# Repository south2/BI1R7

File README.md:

# body interaction vibrator development board

body interaction 1 board, revision 7

The *body interaction 1* is a tiny microcontroller board for building vibrating devices like (sex) toys. 
The vibration strength is controlled by motion. It is equipped with a radio module for wireless data transmission. 
The *body interaction 1* includes a LiPo battery and a capsuled vibration motor. 
Supports the Arduino IDE and Codebender.

*body interaction 1* is small, cheap and you can start at once. You can program the board with the Arduino software (IDE) or in a web browser (eg. codebender). A demo sketch is already uploaded to the board. Download 3D cases from [Thingiverse](http://www.thingiverse.com), print them, assemble the *body interaction 1* and have fun! Or invent your own toy using 3d modelling software.

#### More technical staff
*body interaction 1* has a Atmel Attiny84 on board, a LiPo charger (via USB) and a LiPo battery. The encapsuled vibration motor is controlled with PWM, though you can vary the vibration strength as needed. There are two additional I/O ports which can be used for other sensors or actuators. Programming is done with an ISP interface (2×3 pole header). The board has BMA020 accelerometer and a RFM12B (915 or 868 Mhz) radio module. Size: approx. 20x36mm. Open Source Hardware. Supports the Arduino IDE as well as codebender.
You need an ISP programmer (eg. USB tiny ISP) for uploading *new* programs (sketches) to the *body interaction 1*. There are two options for the wireless transmission chip. You can select 868 MHz (EU) or 915MHz (US, Australia) radio module.

Blog & How-to's: [www.bodyinteraction.com](http://www.bodyinteraction.com)

Download the [Quick start guide](https://projectbodyinteraction.files.wordpress.com/2015/09/quickstartguide-bodyinteraction1.pdf)

3d models at [Thingiverse](http://www.thingiverse.com/south/designs)

Construct your own with the 3d modelling software [Tinkercad](https://www.tinkercad.com/users/3N2Od7pDF0x-bodyinteraction)

Arduino example sketch at [codebender](https://codebender.cc/embed/sketch:96042#p5_fin.ino)

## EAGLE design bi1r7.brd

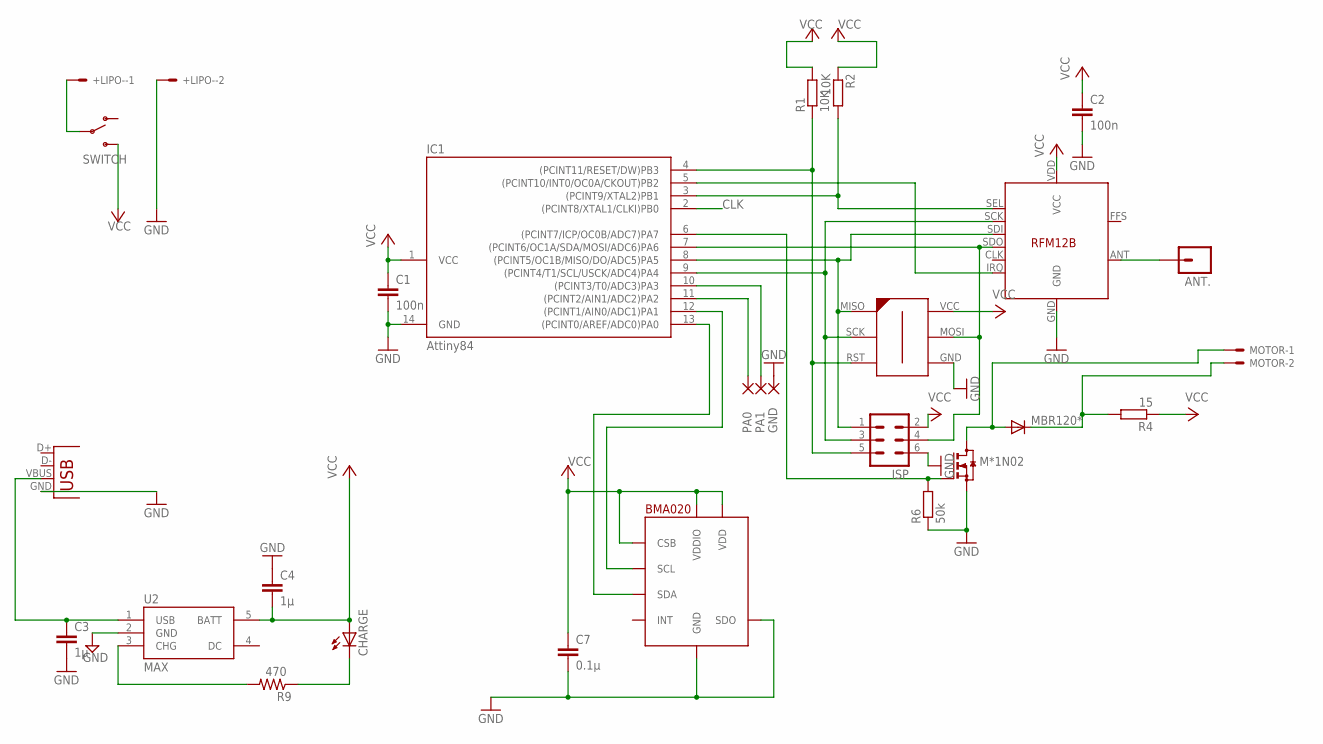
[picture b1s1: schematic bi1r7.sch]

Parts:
+LIPO-: SM02B-SRSS-TB
ANT.: M01PTH; 1X01
BMA020: BMA020; LBA-12
C1, C2: 100n; C0603K
C3, C4: 1µ; 0603-CAP
C7: 0.1µ; 0603-CAP
CHARGE: LED0603; LED-0603
GND: SMD2; SMD1,27-2,54
IC1: Attiny84; SOIC14
ISP: MA03-2S; MA03-2-0.8
M*1N02: BSS123; SOT23
MBR120*: CGRM4001-G; SOD-123_MINI-SMA
MOTOR: SM02B-SRSS-TB
PA0, PA1: SMD2; SMD1,27-2,54
R1, R2: 10K; R0603
R4: 15; R0603
R6: 50k; R0603
R9: 470; R0603
RFM12B: RFM12B
SWITCH: SWITCH-SPDTSMD2; SWITCH-SPDT-SMD
U2: MAX; SOT23-5
U$2: AVR-ISP-6-EDGE; 6PAD_ISP
USB: USB-MICROB

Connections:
CLK: IC1.2 ((PCINT8/XTAL1/CLKI)PB0)
GND: +LIPO-.2, BMA020.P$3 (GND), BMA020.P$7 (SDO), C1.2, C2.2, C3.2, C4.1, C7.2, GND.1, IC1.14 (GND), ISP.6, M*1N02.2 (S), R6.1, RFM12B.GND, U2.2 (GND), U$2.GND, USB.GND
LED: BMA020.P$8 (SDA), IC1.13 ((PCINT0/AREF/ADC0)PA0)
unnamed: IC1.4 ((PCINT11/RESET/DW)PB3), ISP.5, R1.1, U$2.RST
unnamed: IC1.3 ((PCINT9/XTAL2)PB1), R2.2, RFM12B.SEL
unnamed: ANT..1, RFM12B.ANT
unnamed: IC1.9 ((PCINT4/T1/SCL/USCK/ADC4)PA4), ISP.3, RFM12B.SCK, U$2.SCK
unnamed: IC1.8 ((PCINT5/OC1B/MISO/DO/ADC5)PA5), ISP.1, RFM12B.SDI, U$2.MISO
unnamed: IC1.7 ((PCINT6/OC1A/SDA/MOSI/ADC6)PA6), ISP.4, RFM12B.SDO, U$2.MOSI
unnamed: IC1.5 ((PCINT10/INT0/OC0A/CKOUT)PB2), RFM12B.IRQ
unnamed: IC1.6 ((PCINT7/ICP/OC0B/ADC7)PA7), M*1N02.1 (G), R6.2
unnamed: IC1.10 ((PCINT3/T0/ADC3)PA3), PA1.1
unnamed: IC1.11 ((PCINT2/AIN1/ADC2)PA2), PA0.1
unnamed: BMA020.P$6 (SCL), IC1.12 ((PCINT1/AIN0/ADC1)PA1)
unnamed: M*1N02.3 (D), MBR120*.A, MOTOR.1
unnamed: MBR120*.C, MOTOR.2, R4.2
unnamed: C3.1, U2.1 (USB), USB.VBUS
unnamed: +LIPO-.1, SWITCH.2
unnamed: CHARGE.C, R9.1
unnamed: R9.2, U2.3 (CHG)
VCC: BMA020.P$2 (VDD), BMA020.P$5 (CSB), BMA020.P$9 (VDDIO), C1.1, C2.1, C4.2, C7.1, CHARGE.A, IC1.1 (VCC), ISP.2, R1.2, R2.1, R4.1, RFM12B.VDD (VCC), SWITCH.3 (S), U2.5 (BATT), U$2.VCC

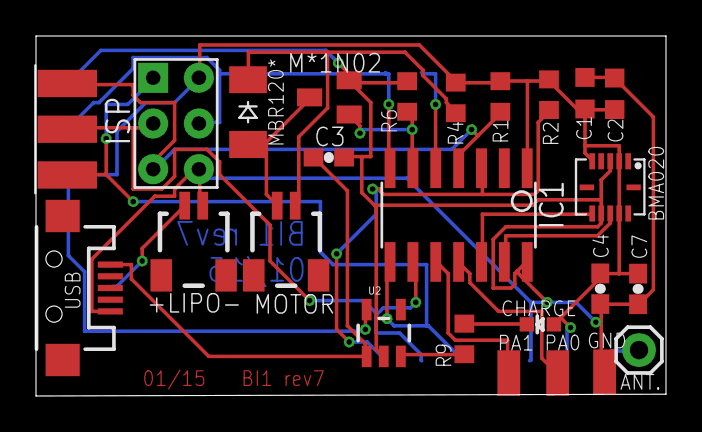
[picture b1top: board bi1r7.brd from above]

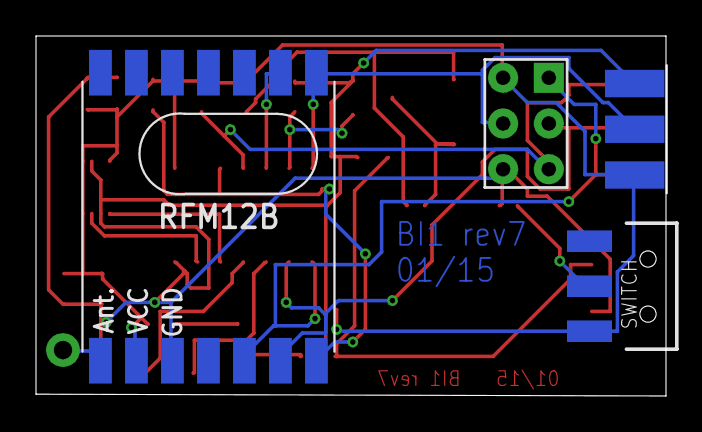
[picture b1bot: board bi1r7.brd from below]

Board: 4 copper layers, 35.0 x 20.0 mm, 27 parts (2 on the bottom side), 20 nets.

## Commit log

2015-04-21 :confetti_ball: Added .gitattributes & .gitignore files
2015-04-21 BRD and SCH and BOM added
2017-07-31 code
    added Arduino code

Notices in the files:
parts and their libraries:
SparkFun: Licensing: CC v3.0 Share-Alike You are welcome to use this library for commercial purposes.
